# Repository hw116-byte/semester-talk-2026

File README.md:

# Semester talk, November 2026

Slides for a lab talk by Weinan Wang and Howard Wang. Draft.

Open the site, then use the arrow keys. `f` is fullscreen, `n` shows speaker notes.

Drawings by Santiago Ramón y Cajal are in the public domain (cover scan: Wellcome Collection, CC BY 4.0).

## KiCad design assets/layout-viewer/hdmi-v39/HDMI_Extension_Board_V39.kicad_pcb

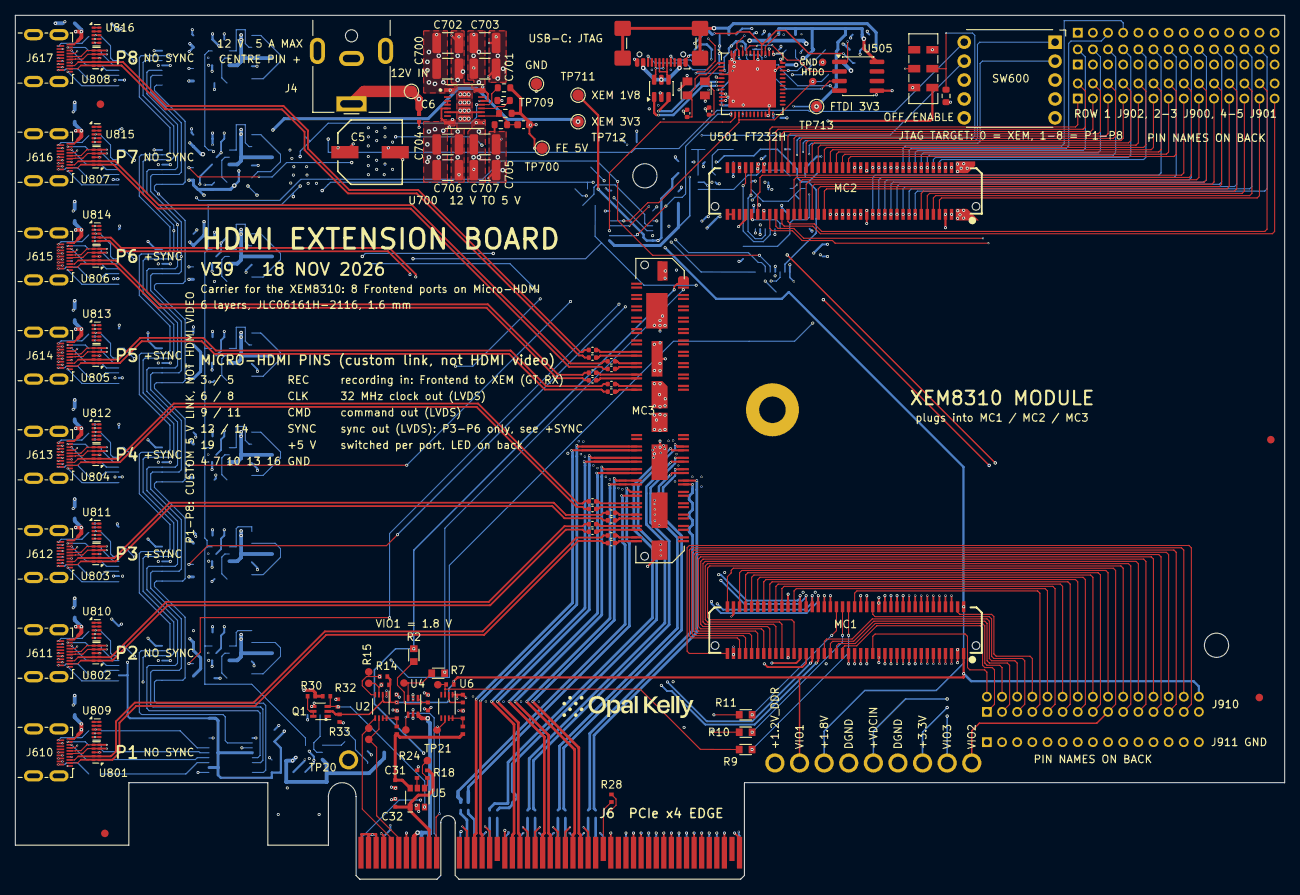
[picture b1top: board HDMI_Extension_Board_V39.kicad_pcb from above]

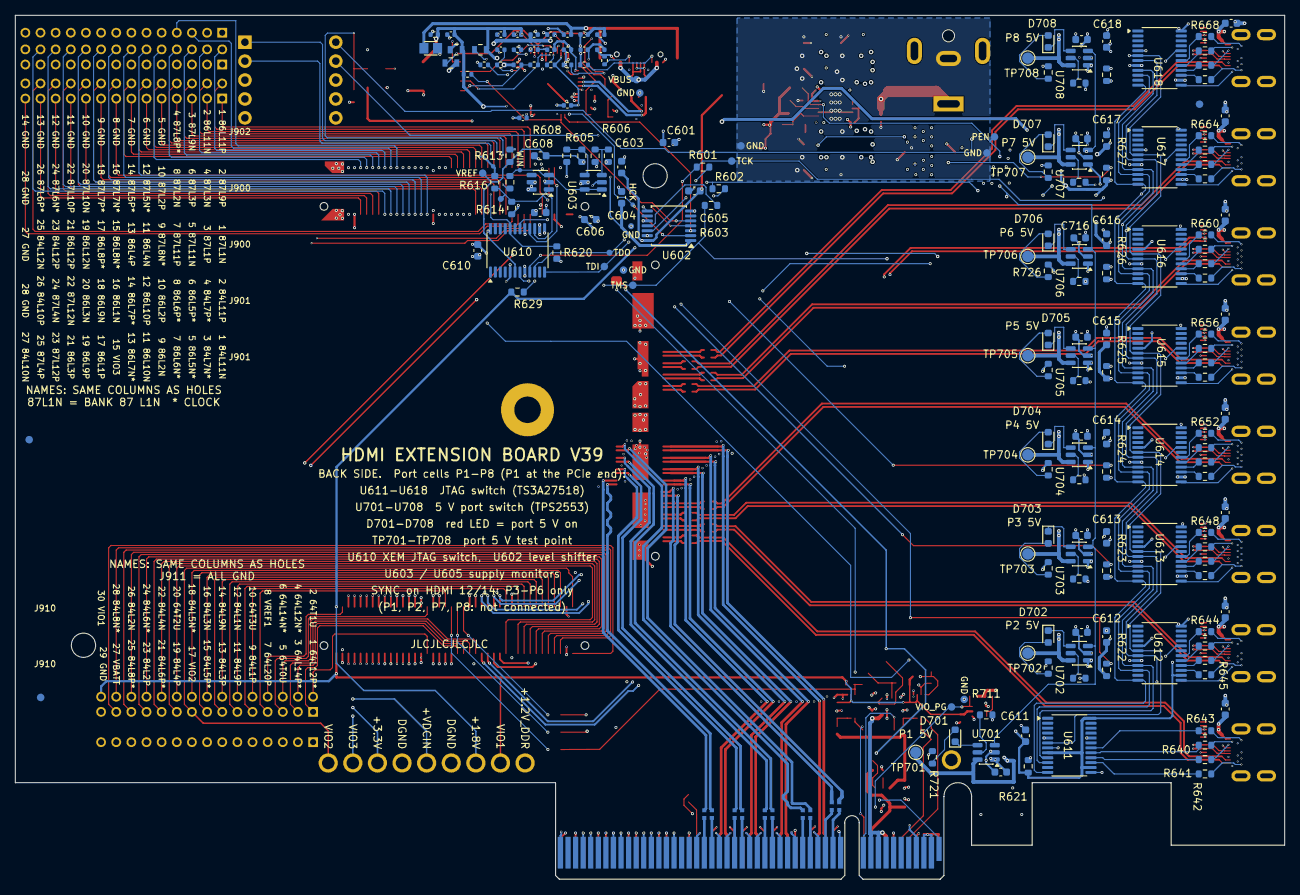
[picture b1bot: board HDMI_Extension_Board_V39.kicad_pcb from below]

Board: 6 copper layers, 167.6 x 114.1 mm, 331 parts (199 on the bottom side), 388 nets.

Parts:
*: Opal Kelly Logo; BRK_Logo_c689e08d
C5: EEE-FK1E221GP; BRK_C5
C6: TMK105BJ104KV-F; BRK_C6
C7: C0402C104K8PACTU; BRK8310_C7
C8: C0402C104K8PACTU; BRK8310_C8
C9: C0402C104K8PACTU; BRK8310_C9
C10: C0402C104K8PACTU; BRK8310_C10
C11: C0402C104K8PACTU; BRK8310_C11
C12: C0402C104K8PACTU; BRK8310_C12
C13: CL05B224KO5NNNC; BRK8310_C13
C14: CL05B224KO5NNNC; BRK8310_C14
C15: CL05B224KO5NNNC; BRK8310_C15
C16: CL05B224KO5NNNC; BRK8310_C16
C17: CL05B224KO5NNNC; BRK8310_C17
C18: CL05B224KO5NNNC; BRK8310_C18
C19: CL05B224KO5NNNC; BRK8310_C19
C20: CL05B224KO5NNNC; BRK8310_C20
C27: C0402C104K8PACTU; BRK8310_C27
C28: C0402C104K8PACTU; BRK8310_C28
C31: C0402C104K8PACTU; BRK8310_C31
C32: C0402C104K8PACTU; BRK8310_C32
C500: 4.7u; C500
C501: 100n; C501
C502: 100n; C502
C503: 18p; C503
C504: 18p; C504
C505: 100n; C505
C506: 100n; C506
C507: 4.7u; C507
C508: 100n; C508
C509: 100n; C509
C510: 100n; C510
C511: 100n; C511
C512: 4.7u; C512
C513: 4.7u; C513
C514: 100n; C514
C515: 4.7u; C515
C516: 100n; C516
C517: 100n; C517
C518: 100n; C518
C519: 10n; C519
C601, C603: 2.2u; C_0603_1608Metric
C604, C605, C606, C609, C610, C611, C612, C613, C614, C615, C616, C617, C618: 100n; C_0603_1608Metric
C608: 1n; C_0603_1608Metric
C700, C701, C702, C703: 10uF; C_1210_3225Metric
C704, C705, C706, C707: 47uF; C_1210_3225Metric
C708: 22pF; C_0603_1608Metric
C711, C712, C713, C714, C715, C716, C717, C718: 100nF; C_0603_1608Metric
C721, C722, C723, C724, C725, C726, C727, C728: 1uF; C_0603_1608Metric
C745, C746, C747, C748, C749, C750, C751, C752, C753, C754, C755, C756, C757, C758, C759, C760: CL05B104KO5NNNC; C_0402_1005Metric
D500: USBLC6-2SC6; D500
D701, D702, D703, D704, D705, D706, D707, D708: RED; LED_0603_1608Metric
FB500: 600R; FB500
FB501: 600R; FB501
FB502: 600R; FB502
FB503: 220R @100MHz; FB503
FID1, FID5, FID6, FID7: FIDUCIAL; BRK_FID1
FID2: FIDUCIAL; BRK_FID2
FID3: FIDUCIAL; BRK_FID3
FID4: FIDUCIAL; BRK_FID4
J4: PJ-063AH; BarrelJack_CUI_PJ-063AH_Horizontal
J6: PCIe x8 Card-Edge Connector; BRK8310_J6
J500: USB4110-GF-A; J500
J610, J611, J612, J613, J614, J615, J616, J617: 467651001; HDMI_Micro-D_Molex_46765-1xxx
J900, J901: Conn_02x14_Odd_Even; HDR_Holes_2x14_P2.00mm
J902: Conn_01x14; HDR_Holes_1x14_P2.00mm
J910: Conn_02x15_Odd_Even; HDR_Holes_2x15_P2.00mm
J911: Conn_01x15; HDR_Holes_1x15_P2.00mm
J920: Voltage test holes; VHoles_1x09_P3.25mm_D1.651
MC1: BTE-040-01-F-D-A; BRK_MC1
MC2: BTE-040-01-F-D-A; BRK_MC2
MC3: QTH-040-01-F-D-DP-A; BRK_MC3
MH2, MH3: Standoff M3; Standoff_Hole_3.2mm_NPTH
Q1: SI1922EDH-T1-GE3; BRK8310_Q1
R2: CRCW06030000Z0EA; BRK8310_R2
R7: CRCW06030000Z0EA; BRK8310_R7
R9: CRCW06030000Z0EA; BRK8310_R9
R10: CRCW06030000Z0EA; BRK8310_R10
R11: CRCW06030000Z0EA; BRK8310_R11
R13: CRCW0402200KFKED; BRK8310_R13
R14: CRCW04024K75FKED; BRK8310_R14
R15: CRCW04024K75FKED; BRK8310_R15
R18: CRCW0402100KFKED; BRK8310_R18
R23: CRCW0402200KFKED; BRK8310_R23
R24: CRCW0402100KFKED; BRK8310_R24
R25: CRCW0402100KFKED; BRK8310_R25
R28: CRCW04020000Z0ED; BRK8310_R28
R30: CRCW04024K75FKED; BRK8310_R30
R31: CRCW04024K75FKED; BRK8310_R31
R32: CRCW0402100KFKED; BRK8310_R32
R33: CRCW0402100KFKED; BRK8310_R33
R500: 5.1k 1%; R500
R501: 5.1k 1%; R501
R502: 100k; R502
R503: 100k; R503
R504: 2k; R504
R505: 10k; R505
R506: 10k; R506
R507: 12k 1%; R507
R509: 10k; R509
R600, R721, R722, R723, R724, R725, R726, R727, R728: 3.3k; R_0603_1608Metric
R601, R602, R603: 22R; R_0603_1608Metric
R605: 301k; R_0603_1608Metric
R606, R608, R616: 100k; R_0603_1608Metric
R607: 402k; R_0603_1608Metric
R613: 68k; R_0603_1608Metric
R614: 4.7k; R_0603_1608Metric
R615: 12k; R_0603_1608Metric
R620, R621, R622, R623, R624, R625, R626, R627, R628, R701, R703: 10k; R_0603_1608Metric
R629: 1k; R_0603_1608Metric
R640, R641, R642, R643, R644, R645, R646, R647, R648, R649, R650, R651, R652, R653, R654, R655, R656, R657, R658, R659, R660, R661, R662, R663, R664, R665, R666, R667, R668, R669, R670, R671: 100R; R_0603_1608Metric
R700: 40.2k; R_0603_1608Metric
R702: 13k; R_0603_1608Metric
R711, R712, R713, R714, R715, R716, R717, R718: 37.4k; R_0603_1608Metric
SW600: SRBQ490100; ALPS_SRBQ490100_1P9T
SW601: JS202011JCQN; SW700
TP9: SMDAT_VIO; BRK8310_TP9
TP10: SMDAT_PCIE; BRK8310_TP10
TP11: SMCLK_PCIE; BRK8310_TP11
TP12: SMCLK_VIO; BRK8310_TP12
TP13: PERST_VIO; BRK8310_TP13
TP14: PERST_PCIE; BRK8310_TP14
TP15: WAKE_VIO; BRK8310_TP15
TP16: WAKE_PCIE; BRK8310_TP16
TP20: +12V_PCIE_C; BRK8310_TP20
TP21: FAULT; BRK8310_TP21
TP700, TP701, TP702, TP703, TP704, TP705, TP706, TP707, TP708, TP709: TestPoint; TestPoint_Pad_D1.5mm
TP710: 12V_IN; TestPoint_Pad_D1.5mm
TP711: 1V8_XEM; TestPoint_Pad_D1.5mm
TP712: 3V3_XEM; TestPoint_Pad_D1.5mm
TP713: 3V3_FTDI; TestPoint_Pad_D1.5mm
TP720, TP721, TP722, TP723, TP725, TP729, TP732, TP733, TP734, TP735, TP736, TP737, TP738, TP739: TestPoint; TestPoint_Pad_D1.0mm
TP724, TP727, TP728: TestPoint; TestPoint_Pad_D0.8mm
TP726, TP730, TP731: TestPoint; TestPoint_Pad_D0.6mm
U2: PCA9306DCUR; BRK8310_U2
U4: SN74AXC1T45DCK; BRK8310_U4
U5: AP22653AW6-7; BRK8310_U5
U6: PCA9306DCUR; BRK8310_U6
U501: FT232HQ-REEL; U501
U505: 93LC56BT-I/SN; SOIC-8_3.9x4.9mm_P1.27mm
U602: TXU0304PWR; TSSOP-14_4.4x5mm_P0.65mm
U603: TPS3700DDCR; SOT-23-6
U605: TPS3808G30DBVR; SOT-23-6
U610, U611, U612, U613, U614, U615, U616, U617, U618: TS3A27518EPWR; TSSOP-24_4.4x7.8mm_P0.65mm
U700: TPSM63606RDLR; TI_TPSM63606_RDL0020A_EVM
U701, U702, U703, U704, U705, U706, U707, U708: TPS2553DBVR; SOT-23-6
U801, U802, U803, U804, U805, U806, U807, U808, U809, U810, U811, U812, U813, U814, U815, U816: TPD4E02B04DQAR; USON-10_2.5x1.0mm_P0.5mm
Y500: 7U12000E18UCG 12MHz; Y500

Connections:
+1.2V_DDR: J920.1, MC3.80, R2.2
+1.8V: C603.1, C605.1, J920.3, MC1.2, R629.2, TP711.1, U602.14
+3.3V: C601.1, C606.1, C609.1, C610.1, C611.1, C612.1, C613.1, C614.1, C615.1, C616.1, C617.1, C618.1, J920.7, MC2.70, R30.2, R31.2, R615.1, R620.1, R621.1, R622.1, R623.1, R624.1, R625.1, R626.1, R627.1, R628.1, SW601.5, TP712.1, U603.5, U605.5, U605.6, U610.8, U610.14, U610.24, U611.8, U611.14, U611.24, U612.8, U612.14, U612.24, U613.8, U613.14, U613.24, U614.8, U614.14, U614.24, U615.8, U615.14, U615.24, U616.8, U616.14, U616.24, U617.8, U617.14, U617.24, U618.8, U618.14, U618.24
+3.3VAUX_PCIE: C31.2, R13.2, R23.2, U5.6
+3.3VAUX_PCIE_C: C32.2, J6.B10, R18.2, U5.1
+3.3V_PCIE_C: C12.2, J6.A9, J6.A10, J6.B8, U4.6
+VDCIN: C5.1, C6.2, C700.1, C701.1, C702.1, C703.1, J4.1, J920.5, MC2.1, MC2.2, MC2.3, MC2.4, TP710.1, U700.1, U700.14, U700.16
/+12V_PCIE_C: J6.A2, J6.A3, J6.B1, J6.B2, J6.B3, TP20.1
/FTDI3V3_PHY: C515.1, C516.1, FB501.2, U501.3
/FTDI3V3_PLL: C513.1, C514.1, FB500.2, U501.8
/FTDI5V_FILTERED: C500.1, C501.1, FB502.2, U501.40
/FTDI_EECLK: R503.2, U501.44, U505.2
/FTDI_EECS: R502.1, U501.45, U505.1
/FTDI_EEDATA: R504.1, U501.43, U505.3
/PCIE_PERST_B_3V3: J6.A11, TP14.1, U4.4
/PCIE_PERST_B_VIO: R7.1, TP13.1, U4.3
/PCIE_PRSNT1_B: J6.A1, R28.2
/PCIE_REFCLKN_C: C8.1, J6.A14
/PCIE_REFCLKP_C: C7.1, J6.A13
/PCIE_RX0N_C: C14.1, J6.A17
/PCIE_RX0P_C: C13.1, J6.A16
/PCIE_RX1N_C: C16.1, J6.A22
/PCIE_RX1P_C: C15.1, J6.A21
/PCIE_RX2N_C: C18.1, J6.A26
/PCIE_RX2P_C: C17.1, J6.A25
/PCIE_RX3N_C: C20.1, J6.A30
/PCIE_RX3P_C: C19.1, J6.A29
/PCIE_SMCLK_3V3: J6.B5, TP11.1, U2.5
/PCIE_SMCLK_VIO: R11.1, R14.1, TP12.1, U2.4
/PCIE_SMDAT_3V3: J6.B6, TP10.1, U2.6
/PCIE_SMDAT_VIO: R10.1, R15.1, TP9.1, U2.3
/PCIE_WAKE_B_3V3: J6.B11, TP16.1, U6.6
/PCIE_WAKE_B_VIO: R9.1, R25.1, TP15.1, U6.3
/VIO_PG: Q1.3, R31.1, R32.2, TP738.1, U5.3
B64_L1N: J614.8, MC1.12, U813.4, U813.7
B64_L1P: J614.6, MC1.10, U813.5, U813.6
B64_L2N: J615.11, MC1.16, U806.5, U806.6
B64_L2P: J615.9, MC1.14, U806.4, U806.7
B64_L3N: J611.11, MC1.15, U802.5, U802.6
B64_L3P: J611.9, MC1.13, U802.4, U802.7
B64_L4N: J614.11, MC1.8, U805.5, U805.6
B64_L4P: J614.9, MC1.6, U805.4, U805.7
B64_L5N: J610.11, MC1.7, U801.5, U801.6
B64_L5P: J610.9, MC1.5, U801.4, U801.7
B64_L6N: J610.8, MC1.11, U809.4, U809.7
B64_L6P: J610.6, MC1.9, U809.5, U809.6
B64_L7N: J612.11, MC1.23, U803.5, U803.6
B64_L7P: J612.9, MC1.21, U803.4, U803.7
B64_L8N: J615.8, MC1.20, U814.4, U814.7
B64_L8P: J615.6, MC1.18, U814.5, U814.6
B64_L9N: J616.11, MC1.24, U807.5, U807.6
B64_L9P: J616.9, MC1.22, U807.4, U807.7
B64_L10N: J616.8, MC1.28, U815.4, U815.7
B64_L10P: J616.6, MC1.26, U815.5, U815.6
B64_L11N_GC: J613.8, MC1.39, U812.4, U812.7
B64_L11P_GC: J613.6, MC1.37, U812.5, U812.6
B64_L12N_GC: J910.4, MC1.43
B64_L12P_GC: J910.1, MC1.41
B64_L13N_GC: J612.8, MC1.27, U811.4, U811.7
B64_L13P_GC: J612.6, MC1.25, U811.5, U811.6
B64_L14N_GC: J910.6, MC1.47
B64_L14P_GC: J910.3, MC1.45
B64_L15N: J613.11, MC1.35, U804.5, U804.6
B64_L15P: J613.9, MC1.33, U804.4, U804.7
B64_L16N: J612.14, MC1.51, U811.1, U811.10
B64_L16P: J612.12, MC1.49, U811.2, U811.9
B64_L17N: MC1.44, R11.2
B64_L17P: MC1.42, R10.2
B64_L18N: J615.14, MC1.56, U814.1, U814.10
B64_L18P: J615.12, MC1.54, U814.2, U814.9
B64_L19N: J611.8, MC1.19, U810.4, U810.7
B64_L19P: J611.6, MC1.17, U810.5, U810.6
B64_L20N: MC1.40, R9.2
B64_L20P: J910.7, MC1.38
B64_L21N: J617.11, MC1.36, U808.5, U808.6
B64_L21P: J617.9, MC1.34, U808.4, U808.7
B64_L22N: J614.14, MC1.52, U813.1, U813.10
B64_L22P: J614.12, MC1.50, U813.2, U813.9
B64_L23N: J613.14, MC1.55, U812.1, U812.10
B64_L23P: J613.12, MC1.53, U812.2, U812.9
B64_L24N: J617.8, MC1.48, U816.4, U816.7
B64_L24P: J617.6, MC1.46, U816.5, U816.6
B64_T0U_N12: J910.5, MC1.32
B64_T1U_N12: J910.2, MC1.31
B64_T2U_N12: J910.20, MC1.57
B64_T3U_N12: J910.10, MC1.58
B67_T3U_N12: MC3.78, R7.2
B84_L1N: J910.12, MC1.64
B84_L1P: J910.9, MC1.62
B84_L2N: J910.26, MC1.71
B84_L2P: J910.23, MC1.69
B84_L3N: J910.16, MC1.72
B84_L3P: J910.13, MC1.70
B84_L4N: J910.22, MC1.63
B84_L4P: J910.19, MC1.61
B84_L5N_HDGC: J910.18, MC1.76
B84_L5P_HDGC: J910.15, MC1.74
B84_L6N_HDGC: J910.24, MC1.67
B84_L6P_HDGC: J910.21, MC1.65
B84_L7N_HDGC: J901.3, MC2.62
B84_L7P_HDGC: J901.4, MC2.60
B84_L8N_HDGC: J910.28, MC1.75
B84_L8P_HDGC: J910.25, MC1.73
B84_L9N: J910.14, MC1.68
B84_L9P: J910.11, MC1.66
B84_L10N: J901.27, MC2.61
B84_L10P: J901.26, MC2.59
B84_L11N: J901.1, MC2.66
B84_L11P: J901.2, MC2.64
B84_L12N: J900.25, MC2.65
B84_L12P: J900.23, MC2.63
B86_L1N: J901.16, MC2.57
B86_L1P: J901.17, MC2.55
B86_L2N: J901.9, MC2.50
B86_L2P: J901.10, MC2.48
B86_L3N: J901.20, MC2.49
B86_L3P: J901.21, MC2.47
B86_L4N: J900.11, MC2.45
B86_L4P: J900.13, MC2.43
B86_L5N_HDGC: J901.5, MC2.58
B86_L5P_HDGC: J901.6, MC2.56
B86_L6N_HDGC: J901.7, MC2.54
B86_L6P_HDGC: J901.8, MC2.52
B86_L7N_HDGC: J901.13, MC2.42
B86_L7P_HDGC: J901.14, MC2.40
B86_L8N_HDGC: J900.15, MC2.41
B86_L8P_HDGC: J900.17, MC2.39
B86_L9N: J901.18, MC2.53
B86_L9P: J901.19, MC2.51
B86_L10N: J901.11, MC2.46
B86_L10P: J901.12, MC2.44
B86_L11N: J902.2, MC2.38
B86_L11P: J902.1, MC2.36
B86_L12N: J900.19, MC2.37
B86_L12P: J900.21, MC2.35
B87_L1N: J900.1, MC2.32
B87_L1P: J900.3, MC2.30
B87_L2N: J900.8, MC2.12
B87_L2P: J900.10, MC2.10
B87_L3N: J900.4, MC2.16
B87_L3P: J900.6, MC2.14
B87_L4N: J901.24, MC2.11
B87_L4P: J901.25, MC2.9
B87_L5N_HDGC: J900.12, MC2.31
B87_L5P_HDGC: J900.14, MC2.29
B87_L6N_HDGC: J900.24, MC2.19
B87_L6P_HDGC: J900.26, MC2.17
B87_L7N_HDGC: J900.16, MC2.27
B87_L7P_HDGC: J900.18, MC2.25
B87_L8N_HDGC: J900.9, MC2.24
B87_L8P_HDGC: J902.4, MC2.22
B87_L9N: J902.3, MC2.20
B87_L9P: J900.2, MC2.18
B87_L10N: J900.20, MC2.23
B87_L10P: J900.22, MC2.21
B87_L11N: J900.5, MC2.28
B87_L11P: J900.7, MC2.26
B87_L12N: J901.22, MC2.15
B87_L12P: J901.23, MC2.13
DGND: C5.2, C6.1, C9.1, C10.1, C11.1, C12.1, C27.1, C28.1, C31.1, C32.1, C500.2, C501.2, C502.2, C503.2, C504.2, C505.2, C506.1, C507.2, C508.2, C509.2, C510.2, C511.2, C512.2, C513.2, C514.2, C515.2, C516.2, C517.1, C518.1, C519.2, C601.2, C603.2, C604.2, C605.2, C606.2, C608.2, C609.2, C610.2, C611.2, C612.2, C613.2, C614.2, C615.2, C616.2, C617.2, C618.2, C700.2, C701.2, C702.2, C703.2, C704.2, C705.2, C706.2, C707.2, C711.2, C712.2, C713.2, C714.2, C715.2, C716.2, C717.2, C718.2, C721.2, C722.2, C723.2, C724.2, C725.2, C726.2, C727.2, C728.2, D500.2, FB503.1, J4.2, J6.A4, J6.A12, J6.A15, J6.A18, J6.A20, J6.A23, J6.A24, J6.A27, J6.A28, J6.A31, J6.A34, J6.A37, J6.A38, J6.A41, J6.A42, J6.A45, J6.A46, J6.A49, J6.B4, J6.B7, J6.B13, J6.B16, J6.B18, J6.B21, J6.B22, J6.B25, J6.B26, J6.B29, J6.B32, J6.B35, J6.B36, J6.B39, J6.B40, J6.B43, J6.B44, J6.B47, J6.B49, J500.A1, J500.A12, J500.B1, J500.B12, J610.4, J610.7, J610.10, J610.13, J610.16, J610.SH, J611.4, J611.7, J611.10, J611.13, J611.16, J611.SH, J612.4, J612.7, J612.10, J612.13, J612.16, J612.SH, J613.4, J613.7, J613.10, J613.13, J613.16, J613.SH, J614.4, J614.7, J614.10, J614.13, J614.16, J614.SH, J615.4, J615.7, J615.10, J615.13, J615.16, J615.SH, J616.4, J616.7, J616.10, J616.13, J616.16, J616.SH, J617.4, J617.7, J617.10, J617.13, J617.16, J617.SH, J900.27, J900.28, J901.28, J902.5, J902.6, J902.7, J902.8, J902.9, J902.10, J902.11, J902.12, J902.13, J902.14, J910.29, J911.1, J911.2, J911.3, J911.4, J911.5, J911.6, J911.7, J911.8, J911.9, J911.10, J911.11, J911.12, J911.13, J911.14, J911.15, J920.4, J920.6, MC1.3, MC1.29, MC1.30, MC1.59, MC1.60, MC1.77, MC1.78, MC2.5, MC2.6, MC2.7, MC2.8, MC2.33, MC2.34, MC2.67, MC2.68, MC2.73, MC3.0, Q1.1, Q1.4, R24.1, R32.1, R33.1, R500.1, R501.2, R502.2, R507.2, R600.2, R606.1, R608.1, R613.2, R616.2, R701.1, R702.1, R711.1, R712.1, R713.1, R714.1, R715.1, R716.1, R717.1, R718.1, SW601.1, SW601.7, TP709.1, TP721.1, TP725.1, TP728.1, TP731.1, TP733.1, TP735.1, TP737.1, TP739.1, U2.1, U4.2, U4.5, U5.2, U6.1, U501.4, U501.9, U501.10, U501.11, U501.22, U501.23, U501.35, U501.36, U501.41, U501.42, U501.47, U501.48, U501.PAD, U505.5, U602.7, U603.2, U605.2, U610.5, U611.5, U612.5, U613.5, U614.5, U615.5, U616.5, U617.5, U618.5, U700.6, U700.11, U700.17, U700.18, U700.19, U700.20, U701.2, U702.2, U703.2, U704.2, U705.2, U706.2, U707.2, U708.2, U801.3, U801.8, U802.3, U802.8, U803.3, U803.8, U804.3, U804.8, U805.3, U805.8, U806.3, U806.8, U807.3, U807.8, U808.3, U808.8, U809.3, U809.8, U810.3, U810.8, U811.3, U811.8, U812.3, U812.8, U813.3, U813.8, U814.3, U814.8, U815.3, U815.8, U816.3, U816.8, Y500.2, Y500.4
DRIVE_ENABLE: R615.2, R616.1, TP727.1, U602.8, U605.1
FE_5V: C704.1, C705.1, C706.1, C707.1, C708.1, C711.1, C712.1, C713.1, C714.1, C715.1, C716.1, C717.1, C718.1, R700.2, R703.2, R721.2, R722.2, R723.2, R724.2, R725.2, R726.2, R727.2, R728.2, TP700.1, U700.5, U700.8, U700.9, U701.1, U702.1, U703.1, U704.1, U705.1, U706.1, U707.1, U708.1
FTDI3V3: C505.1, C507.1, C508.1, C509.1, C510.1, C511.1, C512.1, C604.1, FB500.1, FB501.1, R503.1, R505.2, R506.1, R509.2, TP713.1, U501.12, U501.24, U501.39, U501.46, U505.8, U602.1
GNDADC: MC2.77, MC2.79
HDMI1_JTAG_TCK: J610.17, R640.2
HDMI1_JTAG_TDI: J610.15, R641.2
HDMI1_JTAG_TDO: J610.18, R643.2
HDMI1_JTAG_TMS: J610.2, R642.2
HDMI1_VREF: J610.1, U611.13
HDMI2_JTAG_TCK: J611.17, R644.2
HDMI2_JTAG_TDI: J611.15, R645.2
HDMI2_JTAG_TDO: J611.18, R647.2
HDMI2_JTAG_TMS: J611.2, R646.2
HDMI2_VREF: J611.1, U612.13
HDMI3_JTAG_TCK: J612.17, R648.2
HDMI3_JTAG_TDI: J612.15, R649.2
HDMI3_JTAG_TDO: J612.18, R651.2
HDMI3_JTAG_TMS: J612.2, R650.2
HDMI3_VREF: J612.1, U613.13
HDMI4_JTAG_TCK: J613.17, R652.2
HDMI4_JTAG_TDI: J613.15, R653.2
HDMI4_JTAG_TDO: J613.18, R655.2
HDMI4_JTAG_TMS: J613.2, R654.2
HDMI4_VREF: J613.1, U614.13
HDMI5_JTAG_TCK: J614.17, R656.2
HDMI5_JTAG_TDI: J614.15, R657.2
HDMI5_JTAG_TDO: J614.18, R659.2
HDMI5_JTAG_TMS: J614.2, R658.2
HDMI5_VREF: J614.1, U615.13
HDMI6_JTAG_TCK: J615.17, R660.2
HDMI6_JTAG_TDI: J615.15, R661.2
HDMI6_JTAG_TDO: J615.18, R663.2
HDMI6_JTAG_TMS: J615.2, R662.2
HDMI6_VREF: J615.1, U616.13
HDMI7_JTAG_TCK: J616.17, R664.2
HDMI7_JTAG_TDI: J616.15, R665.2
HDMI7_JTAG_TDO: J616.18, R667.2
HDMI7_JTAG_TMS: J616.2, R666.2
HDMI7_VREF: J616.1, U617.13
HDMI8_JTAG_TCK: J617.17, R668.2
HDMI8_JTAG_TDI: J617.15, R669.2
HDMI8_JTAG_TDO: J617.18, R671.2
HDMI8_JTAG_TMS: J617.2, R670.2
HDMI8_VREF: J617.1, U618.13
HOST_TCK: TP726.1, U501.13, U602.2
HOST_TDI: U501.14, U602.3
HOST_TDO: R509.1, TP732.1, U501.15, U602.5
HOST_TMS: U501.16, U602.4
JTAG_TCK: MC2.76, U610.17
JTAG_TCK_1V8: R601.2, TP720.1, U610.9, U611.9, U612.9, U613.9, U614.9, U615.9, U616.9, U617.9, U618.9
JTAG_TDI: MC2.74, U610.16
JTAG_TDI_1V8: R602.2, TP723.1, U610.12, U611.12, U612.12, U613.12, U614.12, U615.12, U616.12, U617.12, U618.12
JTAG_TDO: MC2.71, U610.18
JTAG_TDO_1V8: TP724.1, U602.10, U610.10, U611.10, U612.10, U613.10, U614.10, U615.10, U616.10, U617.10, U618.10
JTAG_TMS: MC2.72, U610.15
JTAG_TMS_1V8: R603.2, TP722.1, U610.7, U611.7, U612.7, U613.7, U614.7, U615.7, U616.7, U617.7, U618.7
MASTER: R600.1, R614.1, SW601.6
MGT_REFCLK1N_225_C: C8.2, MC3.19
MGT_REFCLK1P_225_C: C7.2, MC3.17
MGT_RXN0_224: C746.1, J610.5, U801.2, U801.9
MGT_RXN0_225: J6.B28, MC3.23
MGT_RXN0_226: C754.1, J614.5, U805.2, U805.9
MGT_RXN1_224: C748.1, J611.5, U802.2, U802.9
MGT_RXN1_225: J6.B24, MC3.27
MGT_RXN1_226: C756.1, J615.5, U806.2, U806.9
MGT_RXN2_224: C750.1, J612.5, U803.2, U803.9
MGT_RXN2_225: J6.B20, MC3.31
MGT_RXN2_226: C758.1, J616.5, U807.2, U807.9
MGT_RXN3_224: C752.1, J613.5, U804.2, U804.9
MGT_RXN3_225: J6.B15, MC3.35
MGT_RXN3_226: C760.1, J617.5, U808.2, U808.9
MGT_RXP0_224: C745.1, J610.3, U801.1, U801.10
MGT_RXP0_225: J6.B27, MC3.21
MGT_RXP0_226: C753.1, J614.3, U805.1, U805.10
MGT_RXP1_224: C747.1, J611.3, U802.1, U802.10
MGT_RXP1_225: J6.B23, MC3.25
MGT_RXP1_226: C755.1, J615.3, U806.1, U806.10
MGT_RXP2_224: C749.1, J612.3, U803.1, U803.10
MGT_RXP2_225: J6.B19, MC3.29
MGT_RXP2_226: C757.1, J616.3, U807.1, U807.10
MGT_RXP3_224: C751.1, J613.3, U804.1, U804.10
MGT_RXP3_225: J6.B14, MC3.33
MGT_RXP3_226: C759.1, J617.3, U808.1, U808.10
MGT_TXN0_225: C20.2, MC3.24
MGT_TXN1_225: C18.2, MC3.28
MGT_TXN2_225: C16.2, MC3.32
MGT_TXN3_225: C14.2, MC3.36
MGT_TXP0_225: C19.2, MC3.22
MGT_TXP1_225: C17.2, MC3.26
MGT_TXP2_225: C15.2, MC3.30
MGT_TXP3_225: C13.2, MC3.34
unnamed: C502.1, FB503.2, J500.M1, J500.M2, J500.M3, J500.M4
unnamed: D701.2, R721.1
unnamed: D701.1, U701.4
unnamed: D702.2, R722.1
unnamed: D702.1, U702.4
unnamed: D703.2, R723.1
unnamed: D703.1, U703.4
unnamed: D704.2, R724.1
unnamed: D704.1, U704.4
unnamed: D705.2, R725.1
unnamed: D705.1, U705.4
unnamed: D706.2, R726.1
unnamed: D706.1, U706.4
unnamed: D707.2, R727.1
unnamed: D707.1, U707.4
unnamed: D708.2, R728.1
unnamed: D708.1, U708.4
unnamed: J6.B31, R28.1
unnamed: J500.A5, R500.2
unnamed: J500.B5, R501.1
unnamed: C746.2, MC3.3
unnamed: C754.2, MC3.43
unnamed: C748.2, MC3.7
unnamed: C756.2, MC3.47
unnamed: C750.2, MC3.11
unnamed: C758.2, MC3.51
unnamed: C752.2, MC3.15
unnamed: C760.2, MC3.55
unnamed: C745.2, MC3.1
unnamed: C753.2, MC3.41
unnamed: C747.2, MC3.5
unnamed: C755.2, MC3.45
unnamed: C749.2, MC3.9
unnamed: C757.2, MC3.49
unnamed: C751.2, MC3.13
unnamed: C759.2, MC3.53
unnamed: Q1.5, Q1.6, R30.1
unnamed: R18.1, TP21.1, U5.4
unnamed: C10.2, R13.1, U2.7, U2.8
unnamed: C11.2, R2.1, U4.1
unnamed: R24.2, U5.5
unnamed: C28.2, R23.1, U6.7, U6.8
unnamed: C503.1, U501.1, Y500.1
unnamed: C504.1, U501.2, Y500.3
unnamed: R507.1, U501.5
unnamed: C518.2, U501.37
unnamed: C517.2, U501.38
unnamed: C519.1, R506.2, U501.34
unnamed: R504.2, R505.1, U505.4
unnamed: R601.1, U602.13
unnamed: R602.1, U602.12
unnamed: R603.1, U602.11
unnamed: R605.2, R606.2, U603.3
unnamed: R607.2, R608.2, U603.4
unnamed: R629.1, U610.13
unnamed: R642.1, U611.15
unnamed: R640.1, U611.17
unnamed: R643.1, U611.18
unnamed: R641.1, U611.16
unnamed: R646.1, U612.15
unnamed: R644.1, U612.17
unnamed: R647.1, U612.18
unnamed: R645.1, U612.16
unnamed: R650.1, U613.15
unnamed: R648.1, U613.17
unnamed: R651.1, U613.18
unnamed: R649.1, U613.16
unnamed: R654.1, U614.15
unnamed: R652.1, U614.17
unnamed: R655.1, U614.18
unnamed: R653.1, U614.16
unnamed: R658.1, U615.15
unnamed: R656.1, U615.17
unnamed: R659.1, U615.18
unnamed: R657.1, U615.16
unnamed: R662.1, U616.15
unnamed: R660.1, U616.17
unnamed: R663.1, U616.18
unnamed: R661.1, U616.16
unnamed: R666.1, U617.15
unnamed: R664.1, U617.17
unnamed: R667.1, U617.18
unnamed: R665.1, U617.16
unnamed: R670.1, U618.15
unnamed: R668.1, U618.17
unnamed: R671.1, U618.18
unnamed: R669.1, U618.16
unnamed: U700.3, U700.4
unnamed: C708.2, R700.1, R701.2, U700.10
unnamed: R702.2, U700.12
unnamed: R711.2, U701.5
unnamed: R712.2, U702.5
unnamed: R713.2, U703.5
unnamed: R714.2, U704.5
unnamed: R715.2, U705.5
unnamed: R716.2, U706.5
unnamed: R717.2, U707.5
unnamed: R718.2, U708.5
unnamed: U809.1, U809.10
unnamed: U809.2, U809.9
unnamed: U810.1, U810.10
unnamed: U810.2, U810.9
unnamed: U815.1, U815.10
unnamed: U815.2, U815.9
unnamed: U816.1, U816.10
unnamed: U816.2, U816.9
PORT1_5V: C721.1, J610.19, TP701.1, U701.6
PORT2_5V: C722.1, J611.19, TP702.1, U702.6
PORT3_5V: C723.1, J612.19, TP703.1, U703.6
PORT4_5V: C724.1, J613.19, TP704.1, U704.6
PORT5_5V: C725.1, J614.19, TP705.1, U705.6
PORT6_5V: C726.1, J615.19, TP706.1, U706.6
PORT7_5V: C727.1, J616.19, TP707.1, U707.6
PORT8_5V: C728.1, J617.19, TP708.1, U708.6
PORT_ENABLE: R703.1, TP736.1, U700.13, U701.3, U702.3, U703.3, U704.3, U705.3, U706.3, U707.3, U708.3
ROTARY_COMMON: SW600.3, SW601.2
SEL_0: R620.2, SW600.1, U610.20
SEL_1: R621.2, SW600.2, U611.20
SEL_2: R622.2, SW600.4, U612.20
SEL_3: R623.2, SW600.5, U613.20
SEL_4: R624.2, SW600.6, U614.20
SEL_5: R625.2, SW600.7, U615.20
SEL_6: R626.2, SW600.8, U616.20
SEL_7: R627.2, SW600.9, U617.20
SEL_8: R628.2, SW600.10, U618.20
USB5V: C506.2, D500.5, FB502.1, J500.A4, J500.A9, J500.B4, J500.B9, TP734.1
USB_DM_CONN: D500.4, J500.A7, J500.B7
USB_DP_CONN: D500.6, J500.A6, J500.B6
USB_D_N: D500.3, U501.6
USB_D_P: D500.1, U501.7
VBATT: J910.27, MC1.79
VIO1: C9.2, C27.2, J910.30, J920.2, MC1.1, Q1.2, R14.2, R15.2, R25.2, R33.2, U2.2, U6.2
VIO2: J910.17, J920.9, MC1.80
VIO3: J901.15, J920.8, MC2.69
VREF1: J910.8, MC1.4
VREF_SELECTED: C608.1, R605.1, R607.1, R613.1, TP729.1, U610.6, U611.6, U612.6, U613.6, U614.6, U615.6, U616.6, U617.6, U618.6
WINDOW_GATE: R614.2, TP730.1, U603.1, U603.6, U605.3
